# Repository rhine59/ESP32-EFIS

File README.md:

# ESP32 EFIS

## Comprehensive project guides (18 October 2026)

- **[RedOne User Guide](docs/REDONE-USER-GUIDE.md)** — owner/pilot/app procedures, commissioning prerequisites, firmware, diagnostics and troubleshooting.
- **[RedOne Architecture and Engineering Guide](docs/REDONE-ARCHITECTURE-GUIDE.md)** — component boundaries, hardware, OTA/recovery trust model, services, tests, operational runbooks and outstanding safety gates.

These guides explicitly distinguish available development functionality from planned or unvalidated production behaviour.

Experimental **supplementary/non-primary** multifunction electronic flight instrument for a non-certified aircraft, based on ESP32-S3 and a single 2.1-inch round 480×480 high-brightness display.

> **Safety:** experimental development hardware/software. It is not a certified or approved primary flight instrument and must not be relied upon as the sole source of attitude, altitude, heading or position information.

## Current development status — 16 September 2026

The software/emulator graphics baseline for Artificial Horizon/PFD, Altimeter and Compass has been accepted in deterministic Espressif QEMU at the real 480×480 framebuffer geometry. Physical hardware validation remains pending; compile or simulation results are not physical validation.

A new **adopted display requirement** adds GNSS position and receiver-reported horizontal accuracy to both the Horizon/PFD and Compass pages. The shared instrument data model and GNSS accuracy classifier are now present in firmware; final 480×480 renderer integration, GNSS receiver selection/acquisition, QEMU acceptance and hardware validation remain pending. See `docs/GNSS_DISPLAY.md`.

GNSS accuracy colour bands are: green <=1 m, light green >1–3 m, yellow >3–10 m, orange >10–30 m, red >30 m; no fix/stale/invalid is red with coordinates removed or obscured. These are project UI categories based on the receiver's horizontal accuracy estimate, not guaranteed error bounds or certification/integrity limits.

**Artificial Horizon / PFD — EXISTING BASELINE ACCEPTED IN QEMU; GNSS OVERLAY PENDING ACCEPTANCE.** Accepted attitude behavior remains unchanged. The new lower GNSS strip must not obscure the primary attitude presentation and has independent validity.

**Altimeter — ACCEPTED IN QEMU.** Existing classic three-pointer, digital altitude, QNH/Kollsman and failure behavior are unchanged.

**Compass — EXISTING BASELINE ACCEPTED IN QEMU; GNSS OVERLAY PENDING ACCEPTANCE.** Magnetic heading remains independent of GNSS. GNSS course is `TRK`, never `HDG`.

**BMI088 software pipeline — IMPLEMENTED, COMPILE-VALIDATED, HARDWARE VALIDATION PENDING.** Sensor-to-aircraft axis/sign mapping remains intentionally gated on physical commissioning.

**BMP585 and RM3100 live acquisition — PLANNED / HARDWARE PENDING.** Pressure-to-altitude calculation exists; physical acquisition and magnetic calibration/tilt-compensated heading remain hardware work.

**GNSS acquisition — REQUIREMENT ADOPTED / RECEIVER NOT YET FROZEN.** The project requires a source that provides valid fix state, WGS84 latitude/longitude and an explicit horizontal accuracy estimate. Satellite count alone must not drive the accuracy colour.

See `docs/PROJECT_STATUS.md`, `docs/GNSS_DISPLAY.md`, `docs/SENSORS.md`, `docs/SIMULATION.md` and `docs/TESTING.md`.

Project checkpoints are recorded chronologically in [`CHANGELOG.md`](CHANGELOG.md). Every future checkpoint must update that change history; GitHub `main` remains the authoritative source of truth.

## Instrument pages

The EFIS has three pages on **one physical round display**, selected by the PEC09 rotary/push control:

1. **Horizon/PFD** — BMI088-based AHRS, pitch/roll and validated auxiliary fields, plus GNSS latitude/longitude and colour-coded position accuracy when valid.
2. **Altimeter** — classic three-pointer presentation using the selected ported BMP585 static-pressure sensor and adjustable QNH.
3. **Compass** — rotating-card presentation using the remotely mounted PNI RM3100-CB absolute-heading source, plus GNSS latitude/longitude and colour-coded position accuracy when valid.

No missing sensor value is replaced by a plausible fallback. Invalid or stale data must be unmistakably invalid.

## Hardware baseline

- Espressif **ESP32-S3-WROOM-1-N16R2** — 16 MB Quad flash / 2 MB Quad PSRAM
- project-specific 68 mm carrier PCB, parked pending physical-interface decisions
- TI **TPS62162-Q1** 3.3 V regulator
- Bosch **BMI088 Shuttle Board 3.0** IMU
- **Adafruit ported BMP585 PID 6413** pressure board
- **PNI RM3100-CB** remotely mounted three-axis magnetometer
- **GNSS receiver/interface: to be selected**; must provide explicit fix validity and horizontal accuracy estimate
- one Newhaven **NHD-2.1-480480AF-ASXP** 480×480 round IPS display
- Adafruit **TPS61169** backlight driver
- Microchip **MCP23008** GPIO expansion
- Bourns **PEC09-2320F-T0015** rotary encoder/push switch
- 5 V USB-C development power

See `BOM.md`, `docs/SENSORS.md`, `docs/HARDWARE.md` and `docs/WIRING.md` for authoritative detail. Procurement state does not imply physical validation.

## Firmware and development environment

`firmware/` is an **ESP-IDF v5.4.4** project named `esp32_efis`. It contains the physical display/control path, fail-obvious data validity, NVS-backed UI settings, explicit synthetic bench simulation, QEMU display backend, BMI088 acquisition, the initial attitude estimator and the shared GNSS accuracy-quality classifier.

The GNSS classifier deliberately centralizes the adopted bands so Horizon and Compass cannot silently use different thresholds. The instrument data model carries latitude, longitude, horizontal accuracy, satellites used, fix type, valid and stale states. Receiver parsing/acquisition and final on-screen drawing remain separate pending implementation tasks.

On macOS:

```bash
cd ~/Documents/Xcode/ESP32-EFIS
git pull
source scripts/efis-env.sh
zsh scripts/build-qemu.sh --clean
zsh scripts/run-qemu.sh
```

Physical hardware builds remain paused until hardware is available. A compile alone must never be recorded as physical validation.

## Simulator and acceptance

`simulator/` contains the SwiftUI development simulator. QEMU remains authoritative for ESP32 RGB565 rendering. Both simulators must be extended with deterministic GNSS cases covering no fix, stale data and every accuracy colour band before the new overlay can be marked accepted. Synthetic coordinates must remain unmistakably simulation data.

## Display baseline

There is **one** Newhaven 2.1-inch 480×480 display. Horizon/PFD, Altimeter and Compass are pages on that same display; they are not separate physical instruments. The panel uses RGB565 and 9-bit serial controller initialization with the existing 30 MHz RGB timing baseline.

GNSS information is deliberately a compact secondary strip. It must not compromise readability of attitude or heading, and real-panel legibility must be checked before the layout is frozen.

## Enclosure

The 3 1/8-inch flight-development enclosure is for the single round display and integrated electronics. Physical fitting and final aircraft interfaces remain pending actual hardware/measurements. See `docs/ENCLOSURE.md`.

## Development principles

The BMI088 is rigidly mounted with physically verified aircraft-axis alignment. Pressure, heading, attitude and GNSS have independent validity/freshness handling. GNSS `TRK` is never magnetic `HDG`; `GS` is never IAS. Receiver-reported accuracy is an estimate, not a guarantee, and poor/stale/no-fix position must fail visibly rather than freezing plausible coordinates.

## Boot, maintenance and diagnostics — 26 September 2026

The production interaction model now starts with a **rotary/push-controlled boot menu**. `START EFIS` is the default selection; `FULL TEST` launches the electrical/component diagnostic harness; `FIRMWARE UPDATE` enters the maintenance networking/OTA workflow. Rotation changes selection and a short press selects. Long-press Back/Cancel remains subject to physical encoder validation.

Firmware update first opens an explicit Wi-Fi connection dialog. Saved SSID/credentials persist in ESP-IDF NVS; production units require encrypted NVS for credentials and provide **Forget network**. Wi-Fi failure never blocks startup of the known-good EFIS. See `docs/OTA_USER_SCENARIO.md`, `docs/PHONE_NETWORK_AND_PUBLIC_OTA.md` and `docs/ELECTRICAL_TEST_HARNESS.md`.

### Persistent fault history

Detected software and hardware faults during normal operation are an adopted persistent-diagnostics requirement. A bounded, flash-wear-conscious non-volatile fault log will survive power cycles and be accessible through **FAULT LOG** on the rotary boot menu. It records stable fault identifiers and useful non-secret diagnostic context while immediate on-screen fail-obvious indications remain authoritative during operation. See `docs/ELECTRICAL_TEST_HARNESS.md` and `docs/PROJECT_STATUS.md`.

### Product licensing

The production architecture now reserves a signed, offline-verifiable product-licence mechanism. Licences are generated by an authorised off-device tool, installed through maintenance provisioning and verified on the EFIS using a public key; the private signing key is never stored on the instrument. The rotary boot menu will expose **LICENSE** status/install/reset functions. Licence state persists across normal firmware updates, while reset is deliberate, logged and separate from Wi-Fi/factory reset. Licensing of optional functions must never compromise fail-obvious instrument behaviour.

### Licence account service architecture — 26 September 2026

**ADOPTED / DESIGN STAGED.** Add a separate Docker service (working name `efis-account`) alongside OTA/admin services. It owns customer accounts, registered EFIS devices, licence entitlements and payment-provider linkage; it does not hold the licence-signing private key in the public web tier.

Device identity uses a provisioned immutable **EFIS Device ID / serial number** as the primary key. The ESP32 factory/eFuse base MAC may be recorded as a secondary hardware fingerprint and registration aid, but MAC address alone is not the licence identity because interface MACs can be derived/changed and MAC exposure is unnecessary for manual licensing.

Online boot-maintenance flow: LICENSE -> Connect Wi-Fi -> identify device -> authenticated account/licence endpoint -> fetch signed licence entitlement -> verify locally -> store in protected NVS -> continue offline. The EFIS must not send a user password; device authentication uses a provisioned device credential/challenge mechanism to be specified. Normal flight startup must not depend on account/payment/network availability.

Offline flow: show Device ID and short registration code/QR-capable text; user obtains a signed licence from the account portal on another device and enters/imports it manually or via USB service. The licence is verified locally with the embedded public verification key.

Payment integration is provider-adapter based. The account service creates checkout/customer-management requests and consumes verified payment webhooks; payment card data is handled by the payment provider, not stored by EFIS services. Payment status changes entitlements; a separate private signing worker/service generates signed licence payloads. Define explicit grace/revocation policy before subscriptions are enabled.

Suggested containers: `efis-account` API/web portal; PostgreSQL account/device/entitlement store; private `efis-license-signer` with tightly restricted signing-key access; existing `efis-ota` and `efis-ota-admin`. Payment provider secrets live only in server-side secret storage.

## Pressure scope — 26 September 2026

ASI/IAS capability has been removed from scope. The BMP585 uses the aircraft **STATIC** pressure connection for altitude/barometric pressure. The EFIS has no PITOT input or differential-pressure airspeed sensor.

## Product identity — 2 October 2026

The adopted development brand is **Lollipop Design**. The EFIS/flight-display product is **RedOne** and the engine-interface product is **BlueOne**. Customer-facing references should therefore use **Lollipop Design RedOne** and **Lollipop Design BlueOne**.

Engineering acronyms and stable implementation identifiers remain valid where they describe technical roles: RedOne is the EFIS; BlueOne is the sensor multiplexer (SMUX/SMUX in existing architecture material). Repository, protocol, Device ID, Docker, OTA and cryptographic identifiers are not automatically renamed by this branding decision. See `docs/BRANDING.md`.

## Customer support chatbot — 27 September 2026

A Dockerized **Lollipop Design RedOne Support** service is staged under `support-service/`. It retrieves approved product documentation, records customer interactions/feedback and builds a candidate Q&A queue. Customer conversations never become authoritative automatically: a human reviewer must validate candidates against current product documents before they enter the validated Q&A database. See `docs/SUPPORT_SERVICE.md` and `support-service/README.md`.

## Server platform — 29 September 2026

The proposed server-side infrastructure baseline is a **£750-class, 64 GB RAM / 1 TB NVMe virtualisation host** running Proxmox VE, with separate production Docker, development/test and monitoring VMs plus an optional k3s lab. Existing Docker Compose services should migrate first without requiring Kubernetes; k3s is a deliberate later evaluation path. This platform supports OTA, accounts/licensing, Lollipop Design RedOne Support and related services and is **not part of the flight hardware baseline**. See `docs/SERVER_PLATFORM.md`.

## AEF-CAN aircraft data bus — 30 September 2026

**ADOPTED / PROTOCOL STAGED.** The project now defines **AEF-CAN (Aircraft Experimental Flight CAN)** as the extensible internal data bus for the proposed Lollipop Design BlueOne sensor multiplexer (SMUX/SMUX), Lollipop Design RedOne display and future aircraft modules. It is deliberately hardware-independent and describes aircraft measurements and validity rather than display presentation.

V1 uses 500 kbit/s Classical CAN with 11-bit identifiers. The current ESP32-S3 TWAI controller requires an external CAN transceiver and is Classical-CAN-only; future CAN FD hardware can be added without redefining the application-level measurement semantics.

The protocol reserves functional CAN-ID ranges for engine, electrical, air data, GNSS/navigation, attitude, fuel, aircraft state, alerts, configuration, diagnostics and logging. It defines canonical wire units, scaled integer encoding, explicit freshness/fault semantics, node discovery/capabilities and major/minor compatibility rules. Producers publish facts; consumers own display units, thresholds and colours.

`protocol/aef-can.yaml` is the machine-readable source of truth. The long-form rationale and implementation/testing rules are in `docs/CAN-PROTOCOL.md`. Future C/C++, Swift and Python codecs/test vectors should be generated or verified from the YAML to prevent firmware/simulator/documentation drift.

The AEF-CAN/SMUX system remains **secondary, supplementary and non-certified**. No CAN value may remain silently presented as live after its freshness timeout.

### Licence negative-test correction — 5 October 2026

The Synology licence harness now distinguishes cryptographic integrity from device binding. Tampered-payload and bad-signature candidates exercise Ed25519 rejection; the wrong-device case uses a correctly signed simulator-only licence for a different immutable Device ID and must be rejected by the explicit Device-ID check while the installed valid licence remains unchanged. `scripts/rebuild-synology.sh` uses direct Docker access and no longer requires interactive `sudo`.

### Licensing simulator checkpoint — 5 October 2026

The Synology licence regression harness now passes the complete current simulator contract: signed acquisition, offline persistence, cryptographic and Device-ID rejection, no-entitlement handling, interrupted replacement recovery, Licence Reset, offline acquisition refusal, corrupt persistent-store detection and signed recovery. Startup discards an orphan temporary candidate after an interrupted replacement and retains the previously committed valid licence.

This closes the Docker/simulator licensing stage. Physical ESP32 protected-NVS, real power-loss atomicity and secure factory provisioning remain separate hardware validation gates.

## Documentation index

- [Synology NAS configuration](docs/SYNOLOGY_CONFIGURATION.md)
- [Lollipop Android app](customer-app/android/README.md)

This is the canonical index to the maintained project documentation. Each link is relative so it works directly in GitHub and in a local clone. Documentation supplied inside third-party `firmware/managed_components` dependencies is intentionally excluded.

### Project control, planning and procurement

- **[Bill of Materials and purchasing checklist](BOM.md)** — Prototype BOM, quantities, sourcing, prices and acquisition/receipt status.
- **[Change history](CHANGELOG.md)** — Chronological implementation and documentation checkpoints; `main` is the authoritative project history.
- **[Project status and decision record](docs/PROJECT_STATUS.md)** — Current implementation/validation state plus adopted, proposed, parked, superseded and rejected design decisions.
- **[Project steps and validation gates](docs/PROJECT_STEPS.md)** — Ordered development stages, dependencies and evidence required before progressing.
- **[Parts selection and sourcing](docs/PARTS_SELECTION.md)** — Reference component choices and purchasing sources for the prototype hardware.
- **[Procurement status checkpoint](docs/PROCUREMENT_STATUS_2026-09-16.md)** — Evidence-based snapshot of delivered and in-transit prototype parts.
- **[Parts cost model](docs/COST_MODEL.md)** — Estimated repeatable production parts cost separated from development equipment and spares.
- **[Branding](docs/BRANDING.md)** — Development product-family naming and branding status.
- **[Complete project manual PDF](docs/generated/MicroSky-Horizon-Complete-Project-Manual.pdf)** — Generated indexed PDF compilation of project documentation for offline/reference use.

### System, hardware and mechanical design

- **[Hardware design](docs/HARDWARE.md)** — Processor, display, sensors, interfaces and reference hardware architecture.
- **[Wiring plan](docs/WIRING.md)** — Prototype electrical architecture and frozen ESP32-S3 GPIO/signal allocation.
- **[Display design](docs/DISPLAY.md)** — Newhaven round-display selection, geometry and display implementation requirements.
- **[Sensor architecture](docs/SENSORS.md)** — Attitude, pressure, magnetic and related sensor roles, validity and freshness rules.
- **[AHRS / attitude solution](docs/AHRS.md)** — BMI088 attitude-estimation implementation, limitations and physical-validation gate.
- **[GNSS display](docs/GNSS_DISPLAY.md)** — Position, accuracy, fix-state and presentation requirements for Horizon and Compass pages.
- **[Calibration](docs/CALIBRATION.md)** — Sensor-error and mechanical-alignment calibration requirements.
- **[Power budget](docs/POWER_BUDGET.md)** — Preliminary current/power estimates and later measurement requirements.
- **[Enclosure](docs/ENCLOSURE.md)** — Flight-development enclosure geometry, controls and mechanical packaging.
- **[Mechanical, materials and thermal standard](docs/MECHANICAL_MATERIALS_AND_THERMAL.md)** — RedOne/SMUX materials, captive fasteners and thermal-management decisions.
- **[Carrier PCB requirements](hardware/pcb/README.md)** — Revision-A custom carrier physical/layout requirements and board role.
- **[Carrier PCB schematic definition](hardware/schematics/CARRIER_PCB_SCHEMATIC.md)** — Authoritative electrical definition for the first custom ESP32-S3 carrier.
- **[KiCad Carrier PCB Revision A](hardware/kicad/carrier_rev_a/README.md)** — KiCad project scope, board construction and principal components.
- **[Electrical POST and test harness](docs/ELECTRICAL_TEST_HARNESS.md)** — Boot-selectable component/interface self-test requirements and failure reporting.
- **[Design suggestion image register](docs/design-suggestions/README.md)** — Non-authoritative visual inspiration register and rules for adopting ideas into the design.
- **[Project images](docs/images/README.md)** — Register of regenerable architecture, roadmap and other documentation graphics.

### Firmware, CAN, SMUX and deployment

- **[Firmware overview](firmware/README.md)** — ESP-IDF target, multi-panel firmware structure and principal firmware capabilities.
- **[Firmware deployment](firmware/DEPLOYMENT.md)** — macOS build, flash and monitor procedure for the ESP32-S3 hardware.
- **[macOS build and QEMU setup](docs/MACOS_BUILD_AND_QEMU_SETUP.md)** — Authoritative Apple-Silicon development environment, ESP-IDF and QEMU runbook.
- **[AEF-CAN protocol](docs/CAN-PROTOCOL.md)** — Adopted aircraft experimental CAN architecture and frozen V1 core wire contract.
- **[Stage 7 SMUX integration](docs/STAGE-7-SMUX.md)** — Provisional Sensor Multiplexer/engine-monitoring expansion and EFIS integration boundary.
- **[Safety and airworthiness](docs/SAFETY.md)** — Experimental supplementary-instrument status, limitations and safety principles.
- **[Testing plan](docs/TESTING.md)** — Progressive validation programme from software through bench/hardware/aircraft testing.

### Simulation and demonstration

- **[Simulation architecture](docs/SIMULATION.md)** — Bench/QEMU simulation policy, synthetic-data annunciation and accepted graphics state.
- **[QEMU video demonstration](docs/DEMONSTRATION.md)** — Procedure and scope for recording the actual firmware renderer running under QEMU.
- **[EFIS simulator](simulator/README.md)** — Swift simulator purpose, operation and relationship to the ESP32 renderer.
- **[Web simulator](efis-web-simulator/README.md)** — Docker browser emulator for boot/maintenance, OTA and licensing workflows without physical hardware.

### OTA and remote updates

- **[Remote firmware updates](docs/REMOTE_UPDATES.md)** — OTA architecture, rollback/fallback policy and ESP32 flash/update design.
- **[OTA image administration](docs/OTA_IMAGE_ADMIN.md)** — Definitive Upload → Publish → Download → Activate administration workflow.
- **[OTA user scenario](docs/OTA_USER_SCENARIO.md)** — User-facing OTA interaction model and separation of publication from activation.
- **[Physical OTA test node](docs/OTA_PHYSICAL_TEST_NODE.md)** — Minimal ESP32-S3 fixture for exercising OTA independently of full EFIS hardware.
- **[Phone networking and public OTA](docs/PHONE_NETWORK_AND_PUBLIC_OTA.md)** — Phone pairing, Wi-Fi/network path and public Synology OTA-access design.
- **[OTA server](ota-server/README.md)** — Containerised OTA server implementation, manifest/image hosting and administration interface.

### Licensing, accounts and customer/service apps

- **[Product licensing specification](docs/LICENSING.md)** — Authoritative entitlement model, trust boundaries and offline licensing rules.
- **[Licensing architecture and flows](docs/LICENSING_ARCHITECTURE_AND_FLOWS.md)** — End-to-end actors, trust boundaries and lifecycle/recovery use cases.
- **[Process workflow architecture](docs/PROCESS_WORKFLOW_ARCHITECTURE.md)** — Process-oriented EFIS Service UX/state-machine design and Advanced diagnostic boundary.
- **[Device registration](docs/DEVICE_REGISTRATION.md)** — Initial ownership claiming, permanent Device ID and account-association design.
- **[Customer accounts and mobile apps](docs/CUSTOMER_ACCOUNT_AND_APPS.md)** — Shared web/iOS/Android account, registration, payment and entitlement architecture.
- **[Production licence service](docs/PRODUCTION-LICENCE-SERVICE.md)** — Synology-hosted production direction, zero-configuration network contract and production-readiness gates.
- **[RedOne licence network architecture and disaster recovery](docs/REDONE-LICENCE-NETWORK-ARCHITECTURE.md)** — Public-first/local-fallback routing, mDNS, pinned TLS, trust boundaries, rebuild, backup and recovery procedure.
- **[EFIS Service iPhone app](ios/EFISService/README.md)** — SwiftUI service/licensing app responsibilities and security boundary.
- **[Customer mobile apps](customer-app/README.md)** — Shared role and security model for the native customer companion applications.
- **[Customer iOS app](customer-app/ios/EFISCustomer/README.md)** — SwiftUI customer-app skeleton, secure storage and planned account/payment integration.
- **[Customer Android app](customer-app/android/README.md)** — Kotlin/Compose customer-app skeleton, Keystore and planned account/payment integration.
- **[Account service](account-service/README.md)** — Prototype account, EFIS registration and entitlement service plus its security boundary.
- **[Licence service development harness](license-service/README.md)** — Development-only challenge, device proof, entitlement and signed-licence vertical slice.
- **[Licence signer](license-signer/README.md)** — Private Ed25519/deterministic-CBOR signing service and key/network isolation boundary.
- **[Licence signer build and deployment](license-signer/BUILD-AND-DEPLOY.md)** — Complete Synology build/run procedure for the private signing service.
- **[RedOne local licence gateway](local-license-gateway/README.md)** — Authenticated LAN fallback gateway, Bonjour discovery and pinned-TLS design.

### Support service

- **[Support-service architecture](docs/SUPPORT_SERVICE.md)** — Customer-support chatbot architecture, approved-document knowledge base and controlled learning loop.
- **[Support-service implementation](support-service/README.md)** — Docker service implementation, runtime/configuration and support API details.

### Instrument user guides

- **[User-guide index](docs/user-guides/README.md)** — Entry point for the panel-specific operator documentation.
- **[Artificial Horizon / PFD guide](docs/user-guides/HORIZON.md)** — Horizon presentation, controls, indications and source-validity behaviour.
- **[Altimeter guide](docs/user-guides/ALTIMETER.md)** — Classic analogue/digital altimeter presentation and operating notes.
- **[Compass guide](docs/user-guides/COMPASS.md)** — Rotating compass-card presentation, heading bug and operating conventions.

### Rebuilding generated Xcode projects

The `.xcodeproj` bundles are generated artifacts rather than authoritative source. After a fresh clone, install XcodeGen and run [`scripts/generate-xcode-projects.sh`](scripts/generate-xcode-projects.sh). The tracked `project.yml` files contain the reproducible project configuration.

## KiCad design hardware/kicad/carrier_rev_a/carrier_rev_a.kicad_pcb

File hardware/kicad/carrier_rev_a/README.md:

# Carrier PCB Revision A

KiCad 8-compatible project for the ESP32 Artificial Horizon custom carrier.

- 68 mm circular 4-layer PCB
- ESP32-S3-WROOM-1-N16R2
- TPS62162-Q1 3.3 V buck
- MCP23008 control expander
- USB-C 2.0 device/power input
- direct 40-pin Newhaven FFC
- BMI088, encoder and TPS61169 interfaces
- 60 mm mounting-hole PCD

This is a prototype hardware revision for bench validation. It is not flight-qualified hardware.

## Testability and production follow-on

Revision A remains a bench PCB, but bring-up should preserve access needed by the bootable electrical test harness: power rails, reset/boot, display/backlight controls, MCP23008/encoder and sensor interfaces. The later production carrier adds protected nominal 12 V aircraft power conversion, encrypted-NVS-capable firmware configuration, GNSS and protected external DATA/EXPANSION interfaces. Do not expose raw ESP32 GPIO as aircraft-voltage-tolerant connections.

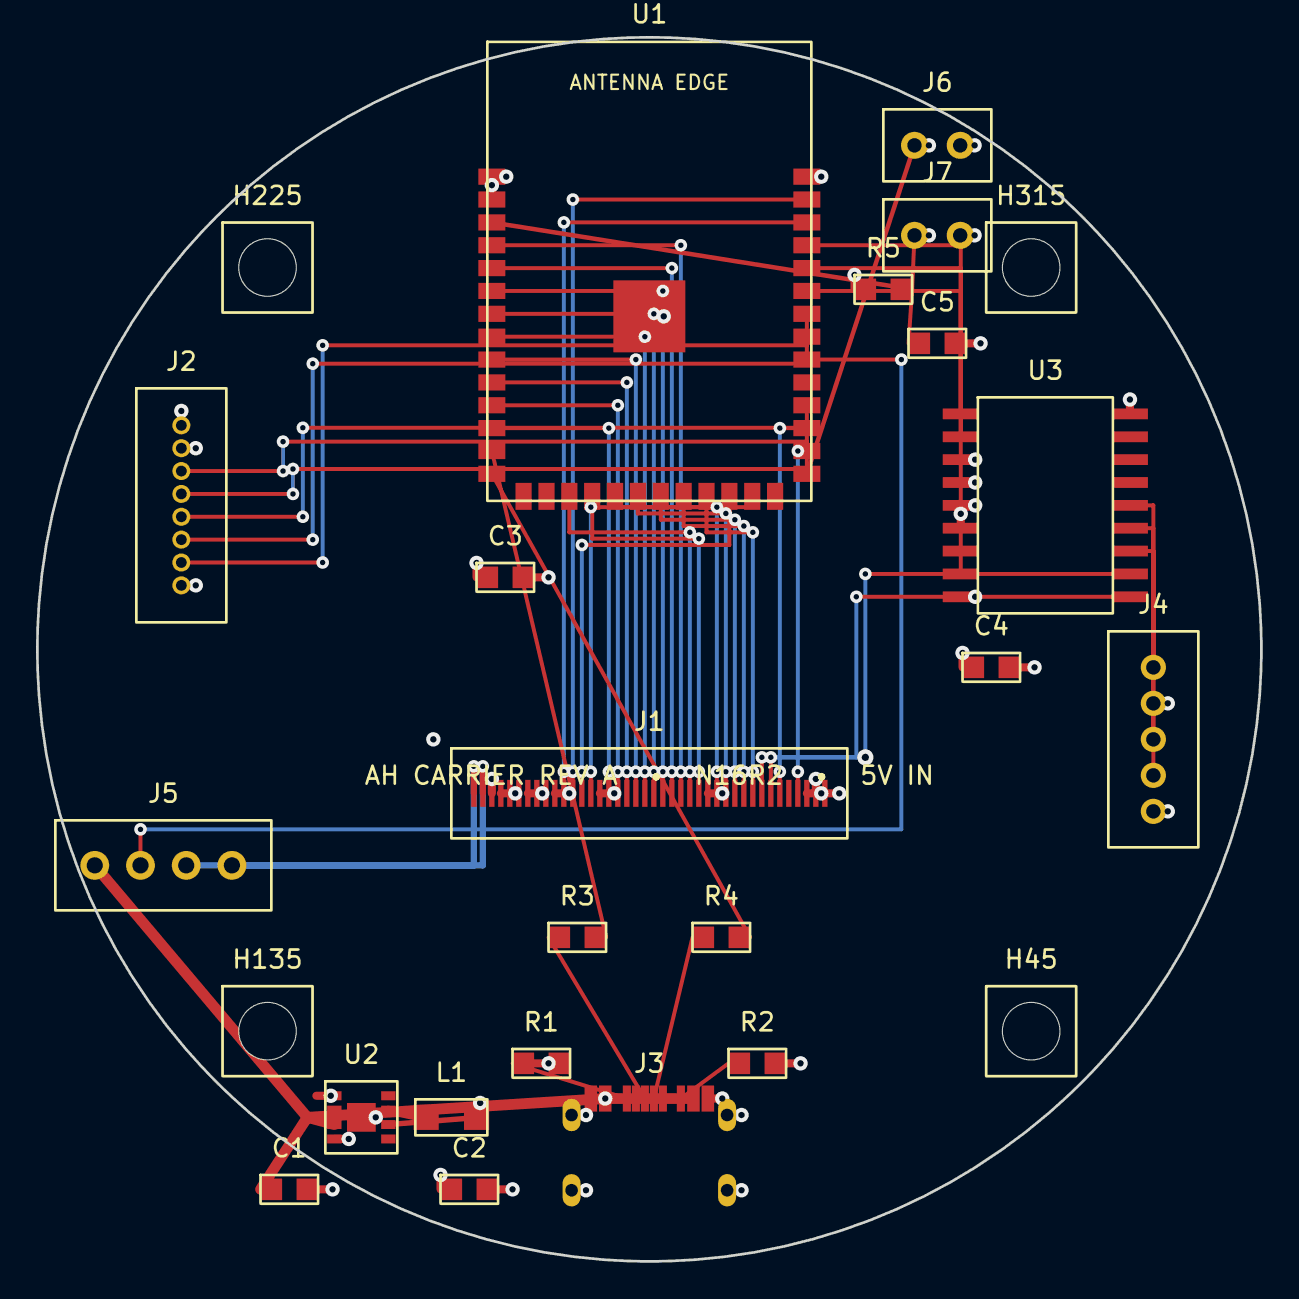
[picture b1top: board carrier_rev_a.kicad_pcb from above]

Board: 4 copper layers, 68.0 x 68.0 mm, 25 parts (0 on the bottom side), 48 nets.

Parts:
C1: 10uF_IN
C2: 22uF_OUT
C3: 100nF_U1
C4: 100nF_U3
C5: 1uF_EN
H45, H135, H225, H315: M2.5_MOUNT
J1: NHD-FFC40-0.5mm
J2: BMI088_HDR
J3: USB_C_Receptacle_HRO_TYPE-C-31-M-12
J4: ENCODER_HDR
J5: TPS61169_HDR
J6: J6_SW_HDR
J7: J7_SW_HDR
L1: 2.2uH
R1: 5.1k_CC1
R2: 5.1k_CC2
R3: 22R_USB_DM
R4: 22R_USB_DP
R5: 10k_EN
U1: ESP32-S3-WROOM-1-N16R2; ESP32-S3-WROOM-1
U2: TPS62162Q1_WSON8
U3: MCP23008-E_SO

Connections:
+3V3: C2.1, C3.1, C4.1, J1.3, J1.39, J2.1, L1.2, R5.1, U1.2, U3.6, U3.18
+5V: C1.1, J3.A4, J3.A9, J3.B4, J3.B9, J5.1, U2.2, U2.3
BL_PWM: J5.2, U1.32
BMI_ACC_CS: J2.6, U1.33
BMI_GYRO_CS: J2.7, U1.34
BOOT: J6.1, U1.27
EN: C5.1, J7.1, R5.2, U1.3
ENC_A: J4.1, U3.12
ENC_B: J4.3, U3.13
ENC_SW: J4.4, U3.14
GND: C1.2, C2.2, C3.2, C4.2, C5.2, J1.4, J1.7, J1.10, J1.15, J1.27, J1.38, J1.40, J2.2, J2.8, J3.A1, J3.A12, J3.B1, J3.B12, J3.S1, J4.2, J4.5, J6.2, J7.2, R1.2, R2.2, U1.1, U1.40, U1.41, U2.1, U2.4, U2.5, U2.9, U3.3, U3.4, U3.5, U3.9
IOX_INT: U1.35, U3.8
IOX_SCL: U1.36, U3.1
IOX_SDA: U1.37, U3.2
LCD_CS: J1.34, U3.10
LCD_D0: J1.16, U1.12
LCD_D1: J1.17, U1.11
LCD_D2: J1.18, U1.10
LCD_D3: J1.19, U1.9
LCD_D4: J1.20, U1.8
LCD_D5: J1.21, U1.7
LCD_D6: J1.22, U1.6
LCD_D7: J1.23, U1.5
LCD_D8: J1.24, U1.4
LCD_D9: J1.25, U1.17
LCD_D10: J1.26, U1.18
LCD_D11: J1.28, U1.19
LCD_D12: J1.29, U1.20
LCD_D13: J1.30, U1.21
LCD_D14: J1.31, U1.22
LCD_D15: J1.32, U1.23
LCD_DE: J1.14, U1.25
LCD_HS: J1.12, U1.39
LCD_PCLK: J1.13, U1.24
LCD_RST: J1.33, U3.11
LCD_VS: J1.11, U1.38
LED_A: J1.2, J5.3
LED_K: J1.1, J5.4
REG_SW: L1.1, U2.7
SPI_MISO: J2.5, U1.30
SPI_MOSI: J1.37, J2.4, U1.28
SPI_SCLK: J1.35, J2.3, U1.29
USB_CC1: J3.A5, R1.1
USB_CC2: J3.B5, R2.1
USB_D+: J3.A6, J3.B6, R4.1
USB_D+_MCU: R4.2, U1.14
USB_D-: J3.A7, J3.B7, R3.1
USB_D-_MCU: R3.2, U1.13

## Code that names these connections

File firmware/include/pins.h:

#pragma once

// ESP32 Artificial Horizon - prototype pin allocation
// Target module: ESP32-S3-WROOM-1-N16R2 on custom carrier PCB
// Supplementary/non-primary flight-development instrument.

// RGB565 display data bus: D0..D15
#define PIN_LCD_D0   4   // panel B1
#define PIN_LCD_D1   5   // panel B2
#define PIN_LCD_D2   6   // panel B3
#define PIN_LCD_D3   7   // panel B4
#define PIN_LCD_D4   8   // panel B5
#define PIN_LCD_D5   9   // panel G0
#define PIN_LCD_D6   10  // panel G1
#define PIN_LCD_D7   11  // panel G2
#define PIN_LCD_D8   12  // panel G3
#define PIN_LCD_D9   13  // panel G4
#define PIN_LCD_D10  14  // panel G5
#define PIN_LCD_D11  15  // panel R1
#define PIN_LCD_D12  16  // panel R2
#define PIN_LCD_D13  17  // panel R3
#define PIN_LCD_D14  18  // panel R4
#define PIN_LCD_D15  21  // panel R5

// RGB timing
#define PIN_LCD_PCLK   1
#define PIN_LCD_DE     2
#define PIN_LCD_HSYNC 38
#define PIN_LCD_VSYNC 39

// Shared configuration/sensor SPI
#define PIN_SPI_MOSI 35
#define PIN_SPI_SCLK 36
#define PIN_SPI_MISO 37

#define PIN_BMI088_ACC_CS  40
#define PIN_BMI088_GYRO_CS 41

// High-brightness backlight PWM
#define PIN_LCD_BACKLIGHT_PWM 42

// MCP23008 I2C bus and interrupt
#define PIN_IOX_SDA 47
#define PIN_IOX_SCL 48
#define PIN_IOX_INT 43
#define MCP23008_ADDR 0x20

// MCP23008 GPIO allocation
#define IOX_LCD_CS      0
#define IOX_LCD_RESET   1
#define IOX_ENCODER_A   2
#define IOX_ENCODER_B   3
#define IOX_ENCODER_SW  4

// Keep GPIO44 unused initially for diagnostics/debug expansion.
#define PIN_SPARE 44

// Native USB on the custom carrier PCB.
#define PIN_USB_DM 19
#define PIN_USB_DP 20

// Deliberately reserved strapping pins:
// GPIO0 = BOOT; GPIO3/GPIO45/GPIO46 have no operational loads.
